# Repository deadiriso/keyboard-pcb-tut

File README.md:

# keyboard-pcb-tut
 First keyboard PCB

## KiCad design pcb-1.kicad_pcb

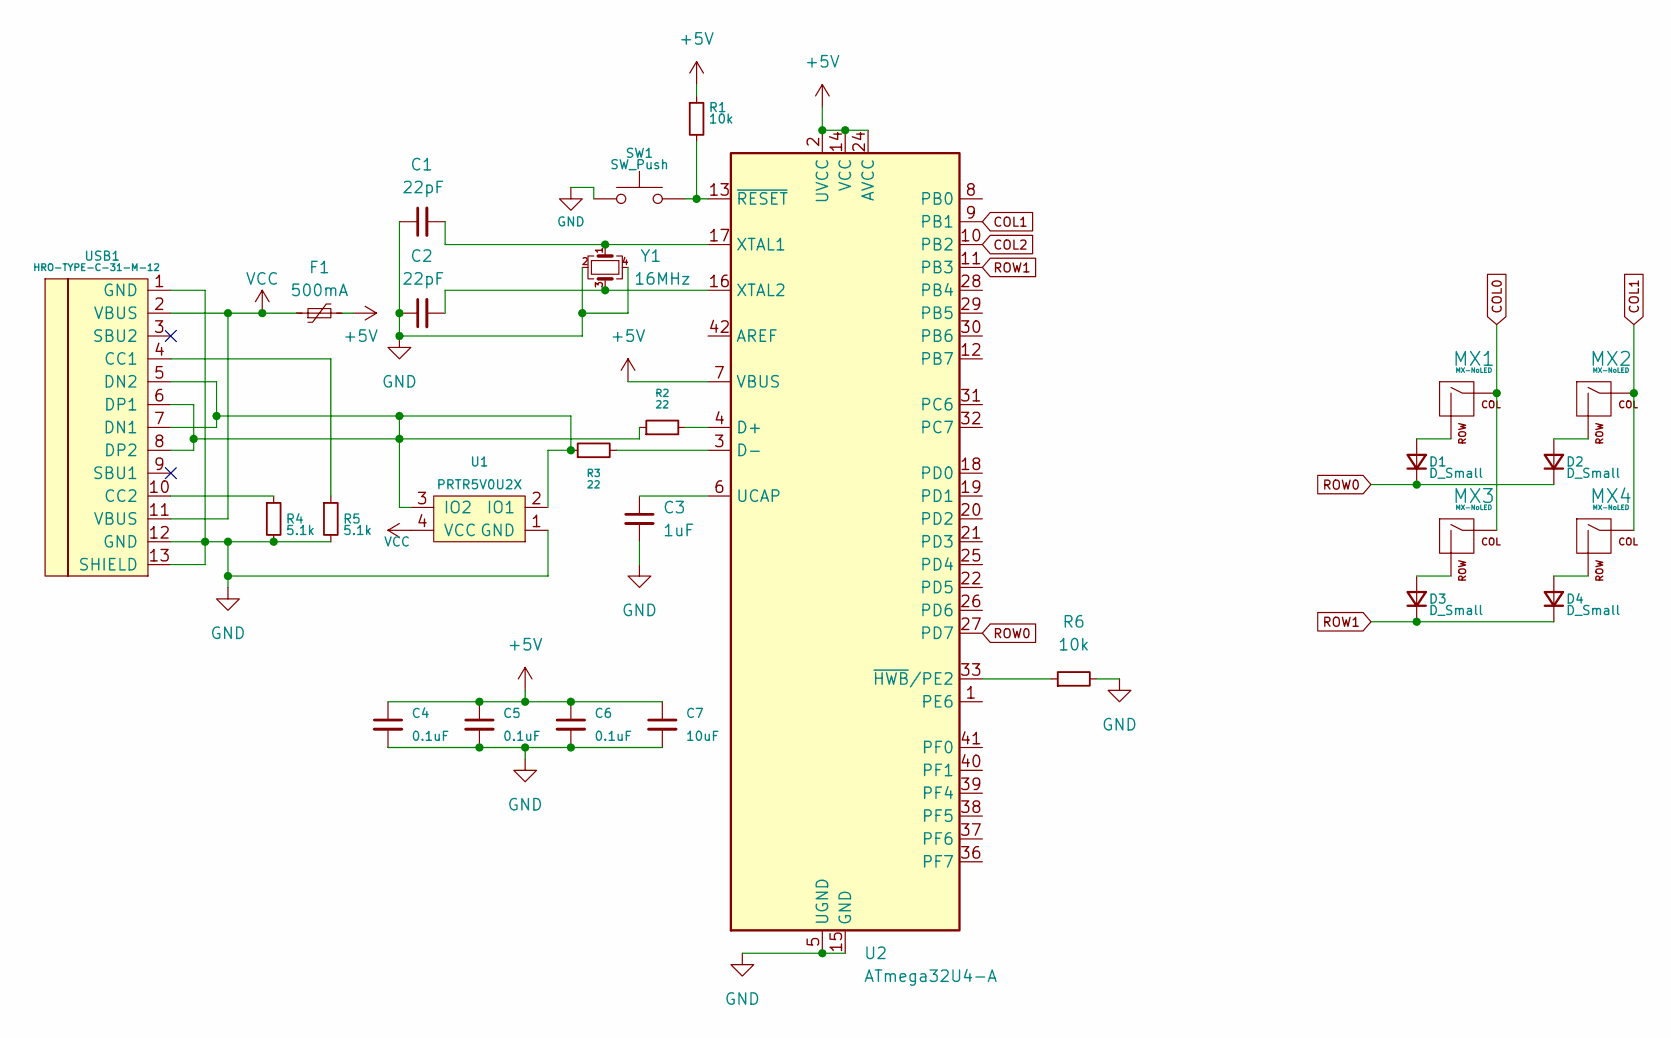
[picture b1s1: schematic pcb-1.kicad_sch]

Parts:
C1, C2: 22pF; C_0805_2012Metric
C3: 1uF; C_0805_2012Metric
C4, C5, C6: 0.1uF; C_0805_2012Metric
C7: 10uF; C_0805_2012Metric
D1, D2, D3, D4: D_Small; D_SOD-123
F1: 500mA; Fuse_1206_3216Metric
MX1, MX2, MX3, MX4: MX-NoLED; MX-1U
R1, R6: 10k; R_0805_2012Metric
R2, R3: 22; R_0805_2012Metric
R4, R5: 5.1k; R_0805_2012Metric
SW1: SW_Push; SKQG-1155865
U1: PRTR5V0U2X; SOT143B
U2: ATmega32U4-A; TQFP-44_10x10mm_P0.8mm
USB1: HRO-TYPE-C-31-M-12
Y1: 16MHz; Crystal_SMD_3225-4Pin_3.2x2.5mm

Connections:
+5V: C4.1, C5.1, C6.1, C7.1, F1.2, R1.1, U2.2 (UVCC), U2.7 (VBUS), U2.14 (VCC), U2.24 (AVCC), U2.34 (VCC), U2.44 (AVCC)
COL0: MX1.1 (COL), MX3.1 (COL)
COL1: MX2.1 (COL), MX4.1 (COL), U2.9 (PB1)
COL2: U2.10 (PB2)
GND: C1.1, C2.1, C3.2, C4.2, C5.2, C6.2, C7.2, R4.2, R5.2, R6.2, SW1.1, U1.1 (GND), U2.5 (UGND), U2.15 (GND), U2.23 (GND), U2.35 (GND), U2.43 (GND), USB1.1 (GND), USB1.12 (GND), USB1.13 (SHIELD), Y1.2, Y1.4
unnamed: C1.2, U2.17 (XTAL1), Y1.1
unnamed: C2.2, U2.16 (XTAL2), Y1.3
unnamed: C3.1, U2.6 (UCAP)
unnamed: D1.2 (A), MX1.2 (ROW)
unnamed: D2.2 (A), MX2.2 (ROW)
unnamed: D3.2 (A), MX3.2 (ROW)
unnamed: D4.2 (A), MX4.2 (ROW)
unnamed: R1.2, SW1.2, U2.13 (~RESET)
unnamed: R2.2, U2.4 (D+)
unnamed: R3.2, U2.3 (D-)
unnamed: R4.1, USB1.10 (CC2)
unnamed: R5.1, USB1.4 (CC1)
unnamed: R6.1, U2.33 (~HWB/PE2)
ROW0: D1.1 (K), D2.1 (K), U2.27 (PD7)
ROW1: D3.1 (K), D4.1 (K), U2.11 (PB3)
VCC: F1.1, U1.4 (VCC), USB1.2 (VBUS), USB1.11 (VBUS)

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
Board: 2 copper layers, 27 parts (0 on the bottom side), 22 nets, no tracks yet.

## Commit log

2022-05-26 Initialize Project
2022-05-26 Add submodules
2022-05-26 Add footprint/symbol libraries
2022-05-26 MCU Schem
2022-05-26 Finished Schematic
2022-05-27 PCB Preparation
